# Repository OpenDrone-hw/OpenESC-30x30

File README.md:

# OpenESC-30x30

Open source 4-in-1 BLDC ESC with a 30.5 x 30.5 mm mounting pattern, part of the
incutec OpenDrone line. Four independent motor controllers, each with its own
MCU, gate driver and six MOSFETs, running AM32 and taking DShot over the
standard 8-pin connector.

Maintained by [@Just4Stan](https://github.com/Just4Stan).

## Specifications

| | |
|---|---|
| Continuous | 60 A / channel |
| Firmware | AM32 |
| ESC protocol | DShot, bidirectional |
| Telemetry | Extended DShot |
| Input | 2-8S LiPo (6.0-33.6 V) |
| BEC | None |
| MCU | One per motor |
| MOSFETs | 6 per motor |
| Current sense | On-board, 330 A |
| FC connector | JST-SH 8-pin |
| Mounting | 30.5 x 30.5 mm, 4.0 mm holes |
| Dimensions | 41.6 x 42.5 mm |
| PCB | 6-layer, 1.6 mm, 2 oz copper |

Technical write-up, part list and layout constraints: [AGENTS.md](AGENTS.md).

## In the line

What pairs with what, and what is available:
[opendrone.be](https://opendrone.be).

## Contributing

See [CONTRIBUTING.md](CONTRIBUTING.md).

## License

Hardware licensed under [CERN-OHL-S-2.0](https://ohwr.org/cern_ohl_s_v2.txt),
see [LICENSE](LICENSE).

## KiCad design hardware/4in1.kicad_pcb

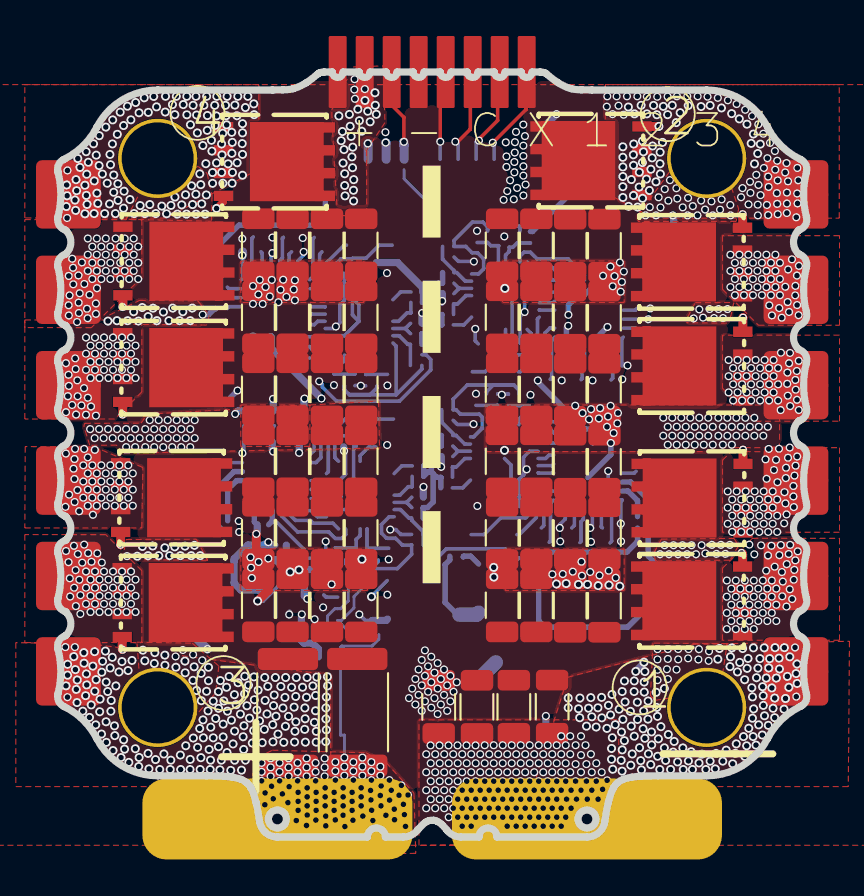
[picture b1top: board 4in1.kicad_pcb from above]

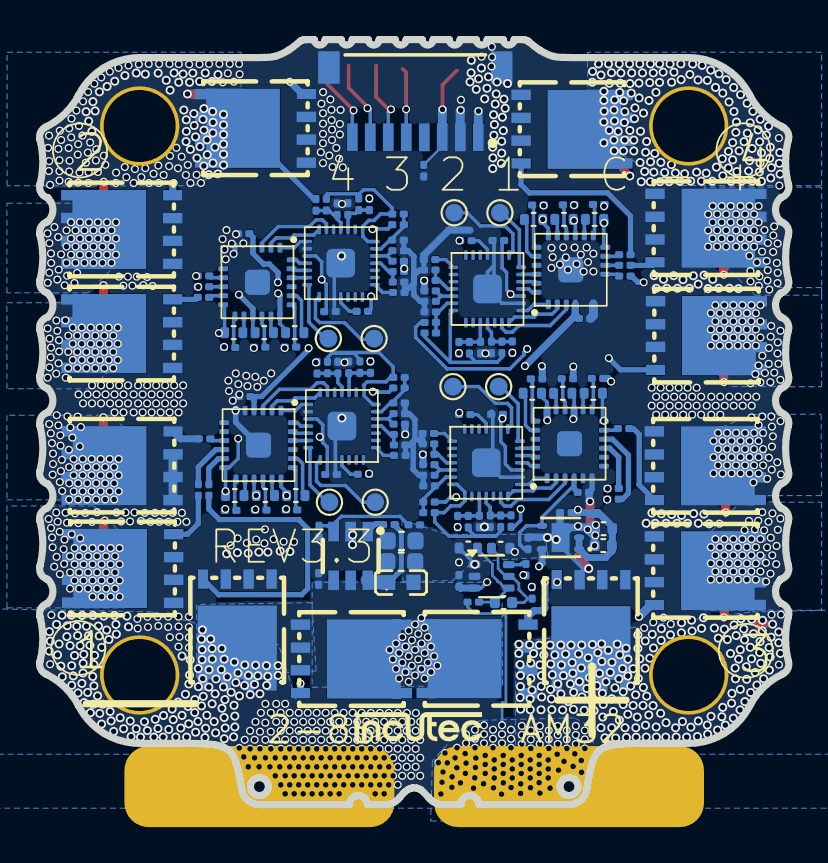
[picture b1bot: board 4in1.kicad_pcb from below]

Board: 6 copper layers, 41.6 x 42.5 mm, 222 parts (157 on the bottom side), 152 nets.

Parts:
C2, C2#2, C3, C3#2, C6, C8, C9, C13, C13#2, C13#3, C14, C14#2, C14#3, C17, C18, C26, C26#2, C26#3, C27, C27#2, C27#3, C30, C43, C43#2, C43#3, C44, C44#2, C44#3, C69, C70, C82, C82#2, C82#3, C83, C83#2, C83#3, C84, C84#2, C84#3, C85, C85#2, C85#3, C96, C97, C98, C99, C107, C107#2, C107#3, C108, C108#2, C108#3: 4.7uF; C_1206_3216Metric
C4, C51: 22uF; C_0402_1005Metric
C32, C33, C34, C35, C36, C37, C38, C39, C40, C41, C53, C56, C62, C67: 100nF; C_0402_WIDE
C42: 1uF; C_0402_1005Metric
C47, C86: 22uF; C_0603_1608Metric
C48, C49, C50, C52, C54, C55, C57, C58, C59, C60, C61, C63, C64, C65, C66, C68, C74, C75, C76, C81, C93, C94: 100nF; C_0201_0603Metric
J1: SM08B-SRSS-TB; JST_SM08B-SRSS-TB
Q1, Q2, Q3, Q4, Q5, Q6, Q7, Q8, Q9, Q10, Q11, Q12, Q13, Q14, Q15, Q16, Q17, Q18, Q19, Q20, Q21, Q22, Q23, Q24: SP40N01GHNK; PDFN-8L_L6.0-W5.0-P1.27
R10, R12, R13, R15, R25, R27, R28, R30, R31, R33, R34, R36, R46, R48, R49, R51, R52, R54, R64, R66, R67, R69, R70, R72: 10k; C_0201_0603Metric
R11, R14, R26, R29, R32, R35, R47, R50, R53, R65, R68, R71, R73, R89, R90: 1k; C_0201_0603Metric
R18, R19, R21, R22, R40, R41, R58, R59, R121: 10k; R_0201_0603Metric
R20, R39, R57, R87: 220R; R_0201_0603Metric
R23, R24, R37, R38, R42, R43, R44, R45, R55, R56, R60, R61, R62, R63, R74, R75, R76, R77, R78, R79, R80, R81, R82, R83: 15R; R_0201_0603Metric
R84, R85, R86, R88: 10R; R_0201_0603Metric
R120: 115k; R_0201_0603Metric
Rsense1, Rsense2: 0.2mR; R_2512_6332Metric
TP1, TP2, TP3, TP4, TP5, TP6, TP7, TP8: TestPoint; TestPoint_Pad_D1.0mm
U2, U5, U7, U9: AT32F421G8U7; QFN-28_L4.0-W4.0-P0.40-TL-EP2.4
U3: 4in1ESC30x30
U4, U6, U8, U10: NSG2065Q; QFN-24_L4.0-W4.0-P0.50-TL-EP2.8
U12: INA186A3IDCKR; SOT-363_SC-70-6
U13: LMR54406DBVR; SOT-23-6_L2.9-W1.6-P0.95-LS2.8-BR
U14: FTC160808S4R7MBCA; IND-SMD_L1.6-W0.8_FTC160865SR47MBCA
U15: TLV76733DRVR; WSON-6_L2.0-W2.0-P0.65-TL-EP

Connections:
+3V3: C4.2, C49.1, C51.2, C55.1, C61.1, C66.1, C81.1, C93.1, R18.2, R21.2, R40.2, R58.2, R84.2, R85.2, R86.2, R88.2, U2.17 (VDD), U5.17 (VDD), U7.17 (VDD), U9.17 (VDD), U12.3 (VS), U15.1 (OUT), U15.2 (FB/SNS)
+10V: C47.1, C57.1, C58.1, C63.1, C68.1, C76.1, C86.1, R120.1, U4.4 (VCC), U6.4 (VCC), U8.4 (VCC), U10.4 (VCC), U14.2, U15.4 (EN), U15.6 (IN)
+BATT: C2.1, C2#2.1, C3.1, C3#2.1, C6.1, C8.1, C9.1, C13.1, C13#2.1, C13#3.1, C14.1, C14#2.1, C14#3.1, C17.1, C18.1, C26.1, C26#2.1, C26#3.1, C27.1, C27#2.1, C27#3.1, C30.1, C43.1, C43#2.1, C43#3.1, C44.1, C44#2.1, C44#3.1, C69.1, C70.1, C74.1, C82.1, C82#2.1, C82#3.1, C83.1, C83#2.1, C83#3.1, C84.1, C84#2.1, C84#3.1, C85.1, C85#2.1, C85#3.1, C96.1, C97.1, C98.1, C99.1, C107.1, C107#2.1, C107#3.1, C108.1, C108#2.1, C108#3.1, J1.1, Q1.3 (D), Q6.3 (D), Q7.3 (D), Q8.3 (D), Q9.3 (D), Q10.3 (D), Q13.3 (D), Q16.3 (D), Q17.3 (D), Q18.3 (D), Q19.3 (D), Q20.3 (D), R89.2, Rsense1.2, Rsense2.2, U3.3 (VBAT+), U13.4 (EN), U13.5 (VIN)
/CSA+: R90.2, Rsense1.1, Rsense2.1, U3.1 (VBAT)
/CURR: C94.1, J1.3, R73.1, U3.5 (CUR)
/ESC1/AH: U2.20 (PA10), U4.22 (HIN1)
/ESC1/AL: U2.15 (PB1), U4.1 (LIN1)
/ESC1/BH: U2.19 (PA9), U4.23 (HIN2)
/ESC1/BL: U2.14 (PB0), U4.2 (LIN2)
/ESC1/CH: U2.18 (PA8), U4.24 (HIN3)
/ESC1/CL: U2.13 (PA7), U4.3 (LIN3)
/ESC1/FBA: R25.1, R26.2, R27.2, U2.6 (PA0)
/ESC1/FBB: R28.2, R29.2, R30.2, U2.10 (PA4)
/ESC1/FBC: R31.2, R32.2, R33.2, U2.11 (PA5)
/ESC1/FBCOMMON: R25.2, R28.1, R31.1, U2.7 (PA1)
/ESC1/GHA: R76.1, U4.19 (HO1)
/ESC1/GHB: R55.1, U4.16 (HO2)
/ESC1/GHC: R23.1, U4.13 (HO3)
/ESC1/GLA: R80.1, U4.11 (LO1)
/ESC1/GLB: R62.1, U4.10 (LO2)
/ESC1/GLC: R42.1, U4.9 (LO3)
/ESC1/MotorA: C53.1, Q1.1 (S), Q2.3 (D), R27.1, U3.23 (1A), U4.18 (VS1)
/ESC1/MotorB: C32.1, Q6.1 (S), Q11.3 (D), R30.1, U3.22 (1B), U4.15 (VS2)
/ESC1/MotorC: C36.1, Q16.1 (S), Q21.3 (D), R33.1, U3.21 (1C), U4.12 (VS3)
/ESC1/vdda: C48.1, R84.1, U2.5 (VDDA)
/ESC2/AH: U5.20 (PA10), U6.22 (HIN1)
/ESC2/AL: U5.15 (PB1), U6.1 (LIN1)
/ESC2/BH: U5.19 (PA9), U6.23 (HIN2)
/ESC2/BL: U5.14 (PB0), U6.2 (LIN2)
/ESC2/CH: U5.18 (PA8), U6.24 (HIN3)
/ESC2/CL: U5.13 (PA7), U6.3 (LIN3)
/ESC2/FBA: R10.1, R11.2, R12.2, U5.6 (PA0)
/ESC2/FBB: R13.2, R14.2, R15.2, U5.10 (PA4)
/ESC2/FBC: R34.2, R35.2, R36.2, U5.11 (PA5)
/ESC2/FBCOMMON: R10.2, R13.1, R34.1, U5.7 (PA1)
/ESC2/GHA: R77.1, U6.19 (HO1)
/ESC2/GHB: R56.1, U6.16 (HO2)
/ESC2/GHC: R24.1, U6.13 (HO3)
/ESC2/GLA: R81.1, U6.11 (LO1)
/ESC2/GLB: R63.1, U6.10 (LO2)
/ESC2/GLC: R43.1, U6.9 (LO3)
/ESC2/MotorA: C56.1, Q3.3 (D), Q7.1 (S), R12.1, U3.20 (2B), U6.18 (VS1)
/ESC2/MotorB: C33.1, Q8.1 (S), Q12.3 (D), R15.1, U3.19 (2C), U6.15 (VS2)
/ESC2/MotorC: C37.1, Q17.1 (S), Q22.3 (D), R36.1, U3.18 (2A), U6.12 (VS3)
/ESC2/vdda: C54.1, R85.1, U5.5 (VDDA)
/ESC3/AH: U7.20 (PA10), U8.22 (HIN1)
/ESC3/AL: U7.15 (PB1), U8.1 (LIN1)
/ESC3/BH: U7.19 (PA9), U8.23 (HIN2)
/ESC3/BL: U7.14 (PB0), U8.2 (LIN2)
/ESC3/CH: U7.18 (PA8), U8.24 (HIN3)
/ESC3/CL: U7.13 (PA7), U8.3 (LIN3)
/ESC3/FBA: R46.1, R47.2, R48.2, U7.6 (PA0)
/ESC3/FBB: R49.2, R50.2, R51.2, U7.10 (PA4)
/ESC3/FBC: R52.2, R53.2, R54.2, U7.11 (PA5)
/ESC3/FBCOMMON: R46.2, R49.1, R52.1, U7.7 (PA1)
/ESC3/GHA: R78.1, U8.19 (HO1)
/ESC3/GHB: R60.1, U8.16 (HO2)
/ESC3/GHC: R37.1, U8.13 (HO3)
/ESC3/GLA: R82.1, U8.11 (LO1)
/ESC3/GLB: R74.1, U8.10 (LO2)
/ESC3/GLC: R44.1, U8.9 (LO3)
/ESC3/MotorA: C62.1, Q4.3 (D), Q13.1 (S), R48.1, U3.15 (3B), U8.18 (VS1)
/ESC3/MotorB: C34.1, Q9.1 (S), Q14.3 (D), R51.1, U3.16 (3C), U8.15 (VS2)
/ESC3/MotorC: C38.1, Q18.1 (S), Q23.3 (D), R54.1, U3.17 (3A), U8.12 (VS3)
/ESC3/vdda: C60.1, R86.1, U7.5 (VDDA)
/ESC4/AH: U9.20 (PA10), U10.22 (HIN1)
/ESC4/AL: U9.15 (PB1), U10.1 (LIN1)
/ESC4/BH: U9.19 (PA9), U10.23 (HIN2)
/ESC4/BL: U9.14 (PB0), U10.2 (LIN2)
/ESC4/CH: U9.18 (PA8), U10.24 (HIN3)
/ESC4/CL: U9.13 (PA7), U10.3 (LIN3)
/ESC4/FBA: R64.1, R65.2, R66.2, U9.6 (PA0)
/ESC4/FBB: R67.2, R68.2, R69.2, U9.10 (PA4)
/ESC4/FBC: R70.2, R71.2, R72.2, U9.11 (PA5)
/ESC4/FBCOMMON: R64.2, R67.1, R70.1, U9.7 (PA1)
/ESC4/GHA: R79.1, U10.19 (HO1)
/ESC4/GHB: R61.1, U10.16 (HO2)
/ESC4/GHC: R38.1, U10.13 (HO3)
/ESC4/GLA: R83.1, U10.11 (LO1)
/ESC4/GLB: R75.1, U10.10 (LO2)
/ESC4/GLC: R45.1, U10.9 (LO3)
/ESC4/MotorA: C67.1, Q5.3 (D), Q19.1 (S), R66.1, U3.12 (4A), U10.18 (VS1)
/ESC4/MotorB: C35.1, Q10.1 (S), Q15.3 (D), R69.1, U3.13 (4B), U10.15 (VS2)
/ESC4/MotorC: C39.1, Q20.1 (S), Q24.3 (D), R72.1, U3.14 (4C), U10.12 (VS3)
/ESC4/vdda: C65.1, R88.1, U9.5 (VDDA)
/M1: J1.5, R20.1, U3.7 (M1)
/M2: J1.6, R39.1, U3.8 (M2)
/M3: J1.7, R57.1, U3.9 (M3)
/M4: J1.8, R87.1, U3.10 (M4)
GND: C2.2, C2#2.2, C3.2, C3#2.2, C4.1, C6.2, C8.2, C9.2, C13.2, C13#2.2, C13#3.2, C14.2, C14#2.2, C14#3.2, C17.2, C18.2, C26.2, C26#2.2, C26#3.2, C27.2, C27#2.2, C27#3.2, C30.2, C40.2, C41.2, C43.2, C43#2.2, C43#3.2, C44.2, C44#2.2, C44#3.2, C47.2, C48.2, C49.2, C50.2, C51.1, C52.2, C54.2, C55.2, C57.2, C58.2, C59.2, C60.2, C61.2, C63.2, C64.2, C65.2, C66.2, C68.2, C69.2, C70.2, C74.2, C76.2, C81.2, C82.2, C82#2.2, C82#3.2, C83.2, C83#2.2, C83#3.2, C84.2, C84#2.2, C84#3.2, C85.2, C85#2.2, C85#3.2, C86.2, C93.2, C94.2, C96.2, C97.2, C98.2, C99.2, C107.2, C107#2.2, C107#3.2, C108.2, C108#2.2, C108#3.2, J1.2, J1.P1 (MP1), J1.P2 (MP2), Q2.1 (S), Q3.1 (S), Q4.1 (S), Q5.1 (S), Q11.1 (S), Q12.1 (S), Q14.1 (S), Q15.1 (S), Q21.1 (S), Q22.1 (S), Q23.1 (S), Q24.1 (S), R11.1, R14.1, R19.2, R22.2, R26.1, R29.1, R32.1, R35.1, R41.2, R47.1, R50.1, R53.1, R59.2, R65.1, R68.1, R71.1, R121.2, U2.16 (VSS), U2.29 (VSS), U3.2 (BATGND), U3.4 (GND), U3.11 (Hole), U4.6 (COM), U4.25 (COM), U5.16 (VSS), U5.29 (VSS), U6.6 (COM), U6.25 (COM), U7.16 (VSS), U7.29 (VSS), U8.6 (COM), U8.25 (COM), U9.16 (VSS), U9.29 (VSS), U10.6 (COM), U10.25 (COM), U12.1 (REF), U12.2 (GND), U13.2 (GND), U15.3 (GND), U15.5 (GND), U15.7 (EP)
unnamed: Q1.2 (G), R76.2
unnamed: Q2.2 (G), R80.2
unnamed: Q3.2 (G), R81.2
unnamed: Q4.2 (G), R82.2
unnamed: Q5.2 (G), R83.2
unnamed: Q6.2 (G), R55.2
unnamed: Q7.2 (G), R77.2
unnamed: Q8.2 (G), R56.2
unnamed: Q9.2 (G), R60.2
unnamed: Q10.2 (G), R61.2
unnamed: Q11.2 (G), R62.2
unnamed: Q12.2 (G), R63.2
unnamed: Q13.2 (G), R78.2
unnamed: Q14.2 (G), R74.2
unnamed: Q15.2 (G), R75.2
unnamed: Q16.2 (G), R23.2
unnamed: Q17.2 (G), R24.2
unnamed: Q18.2 (G), R37.2
unnamed: Q19.2 (G), R79.2
unnamed: Q20.2 (G), R38.2
unnamed: Q21.2 (G), R42.2
unnamed: Q22.2 (G), R43.2
unnamed: Q23.2 (G), R44.2
unnamed: Q24.2 (G), R45.2
unnamed: R19.1, U2.1 (BOOT0)
unnamed: C50.1, R18.1, U2.4 (NRST)
unnamed: TP1.1 (1_1), U2.21 (PA13)
unnamed: TP4.1 (1_1), U2.22 (PA14)
unnamed: R20.2, U2.25 (PB4)
unnamed: C53.2, U4.20 (VB1)
unnamed: C32.2, U4.17 (VB2)
unnamed: C36.2, U4.14 (VB3)
unnamed: R22.1, U5.1 (BOOT0)
unnamed: C52.1, R21.1, U5.4 (NRST)
unnamed: TP2.1 (1_1), U5.21 (PA13)
unnamed: TP5.1 (1_1), U5.22 (PA14)
unnamed: R39.2, U5.25 (PB4)
unnamed: C56.2, U6.20 (VB1)
unnamed: C33.2, U6.17 (VB2)
unnamed: C37.2, U6.14 (VB3)
unnamed: R41.1, U7.1 (BOOT0)
unnamed: C59.1, R40.1, U7.4 (NRST)
unnamed: TP3.1 (1_1), U7.21 (PA13)
unnamed: TP6.1 (1_1), U7.22 (PA14)
unnamed: R57.2, U7.25 (PB4)
unnamed: C62.2, U8.20 (VB1)
unnamed: C34.2, U8.17 (VB2)
unnamed: C38.2, U8.14 (VB3)
unnamed: R59.1, U9.1 (BOOT0)
unnamed: C64.1, R58.1, U9.4 (NRST)
unnamed: TP7.1 (1_1), U9.21 (PA13)
unnamed: TP8.1 (1_1), U9.22 (PA14)
unnamed: R87.2, U9.25 (PB4)
unnamed: C67.2, U10.20 (VB1)
unnamed: C35.2, U10.17 (VB2)
unnamed: C39.2, U10.14 (VB3)
unnamed: C41.1, C42.2, R90.1, U12.4 (+IN)
unnamed: C40.1, C42.1, R89.1, U12.5 (-IN)
unnamed: R73.2, U12.6 (OUT)
unnamed: C75.2, U13.1 (CB)
unnamed: R120.2, R121.1, U13.3 (FB)
unnamed: C75.1, U13.6 (SW), U14.1

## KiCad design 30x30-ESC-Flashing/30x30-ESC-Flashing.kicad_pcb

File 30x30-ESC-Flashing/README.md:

# 30x30-ESC-Flashing: AM32 SWD flashing station

SWD flashing jig for the **OpenESC-30x30** (`../hardware/4in1`). Retargeted copy
of `OpenESC-20x20/20x20-ESC-Flashing`: same 100 x 100 mm 4-layer layout, same
pogo pins, headers, banana jacks and M3 pattern. Only the ten pogo pins moved,
to the coordinates the 30x30 actually uses.

## Contacts

Ten 1.2 mm SMD pogo pins land on the ESC's B.Cu face, which is where the SWD
test points are:

| Net | Lands on |
|---|---|
| `/SWD1_CLK` … `/SWD4_CLK` | PA14 test point of each channel |
| `/SWD1_DIO` … `/SWD4_DIO` | PA13 test point of each channel |
| `/VBAT`, `GND` | the two battery pads, so the target is powered while flashing |

Channel numbering comes from the ESC schematic sheets (`/ESC1/` … `/ESC4/`), not
from position, so SWD1 really is channel 1.

Four 4-pin headers break out CLK, DIO and GND per channel for the ST-LINK probes.

## Retargeted, not redrawn

```bash
KPY=/Applications/KiCad/KiCad.app/Contents/Frameworks/Python.framework/Versions/Current/bin/python3
$KPY ~/OpenDrone/software/OpenDrone-Scripts/esc/esc_jig_retarget.py \
    ../../OpenESC-20x20/20x20-ESC-Flashing/20x20-ESC-Flashing.kicad_pcb \
    ../hardware/4in1.kicad_pcb --dut 4in1ESC30x30 \
    --strip-tracks --swap-outline 30 --retext "20x20=30x30" \
    --out 30x30-ESC-Flashing.kicad_pcb
```

`--strip-tracks` clears the 20x20 routing, `--swap-outline` replaces the
silkscreen ESC outline with the 30x30 one. **The board is unrouted**: the
copper pours from the template are still in place and no longer match the new
pin positions, so redo them.

## Flashing

Two-stage, as on the 20x20: SWD once per MCU to clear readout protection and
write the AM32 bootloader, then firmware and settings over the DShot signal pin.
Host side is `../../OpenESC-20x20/hardware/flash_openesc20.sh` (OpenOCD,
AT32F421 FAP unlock, verify, `--loop` for batches).

License: hardware CERN-OHL-S-2.0, same as the parent repo.

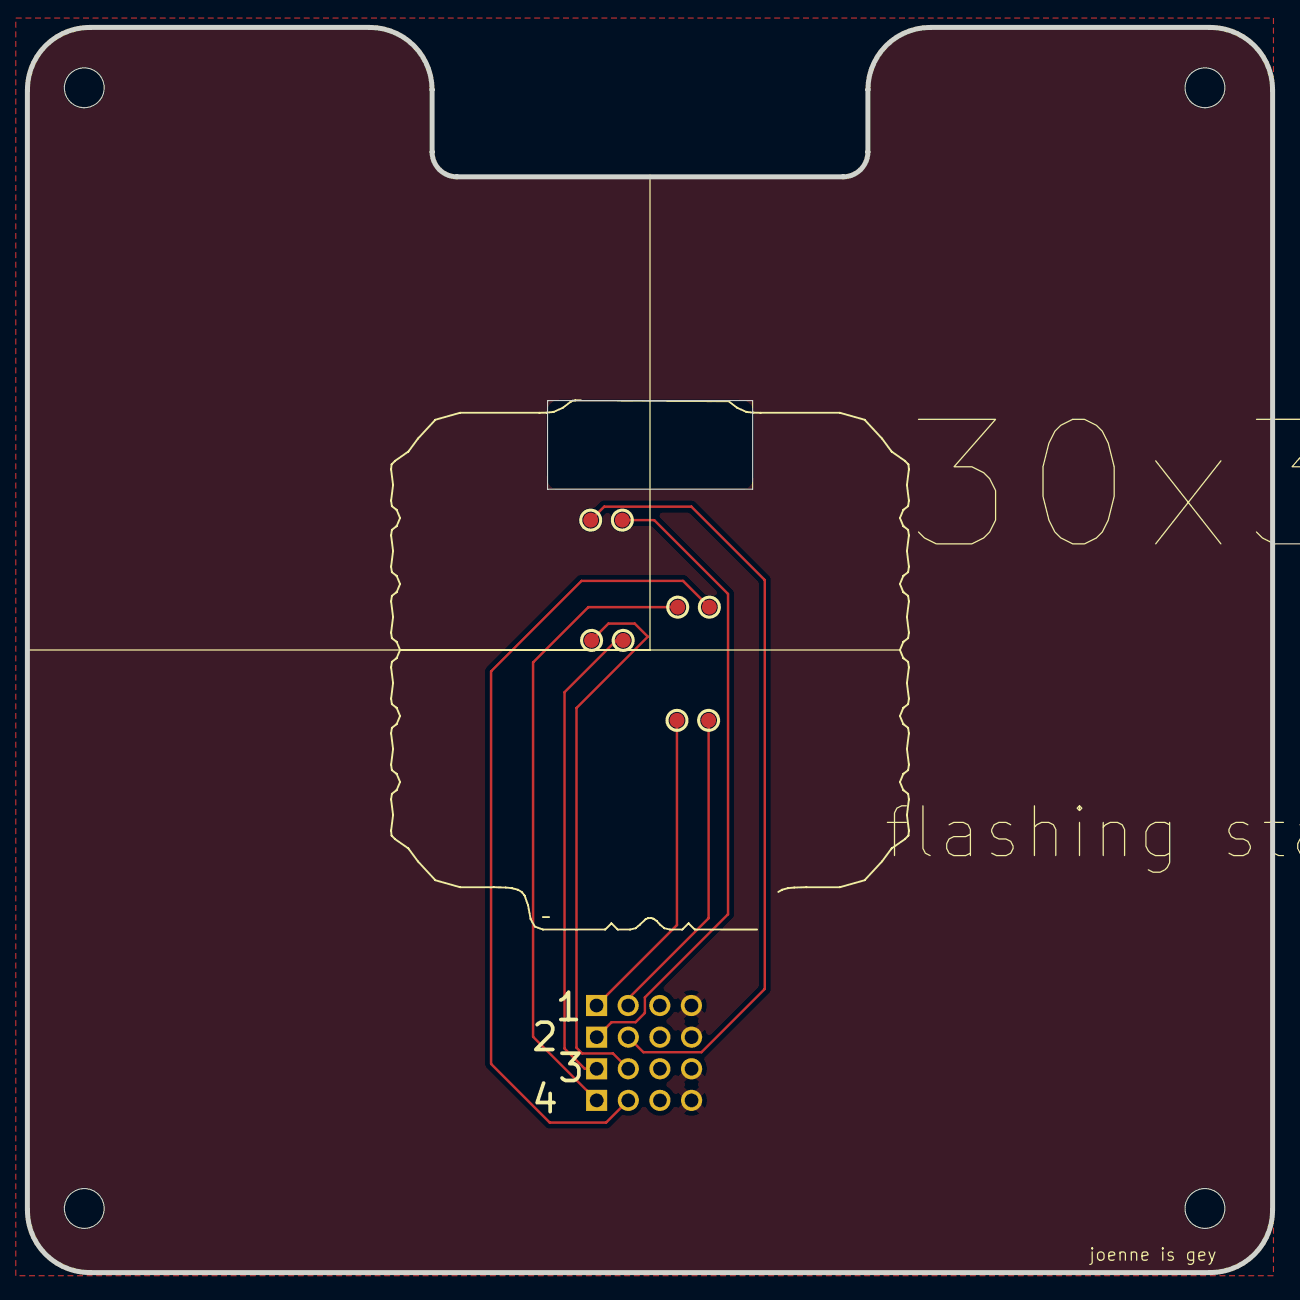
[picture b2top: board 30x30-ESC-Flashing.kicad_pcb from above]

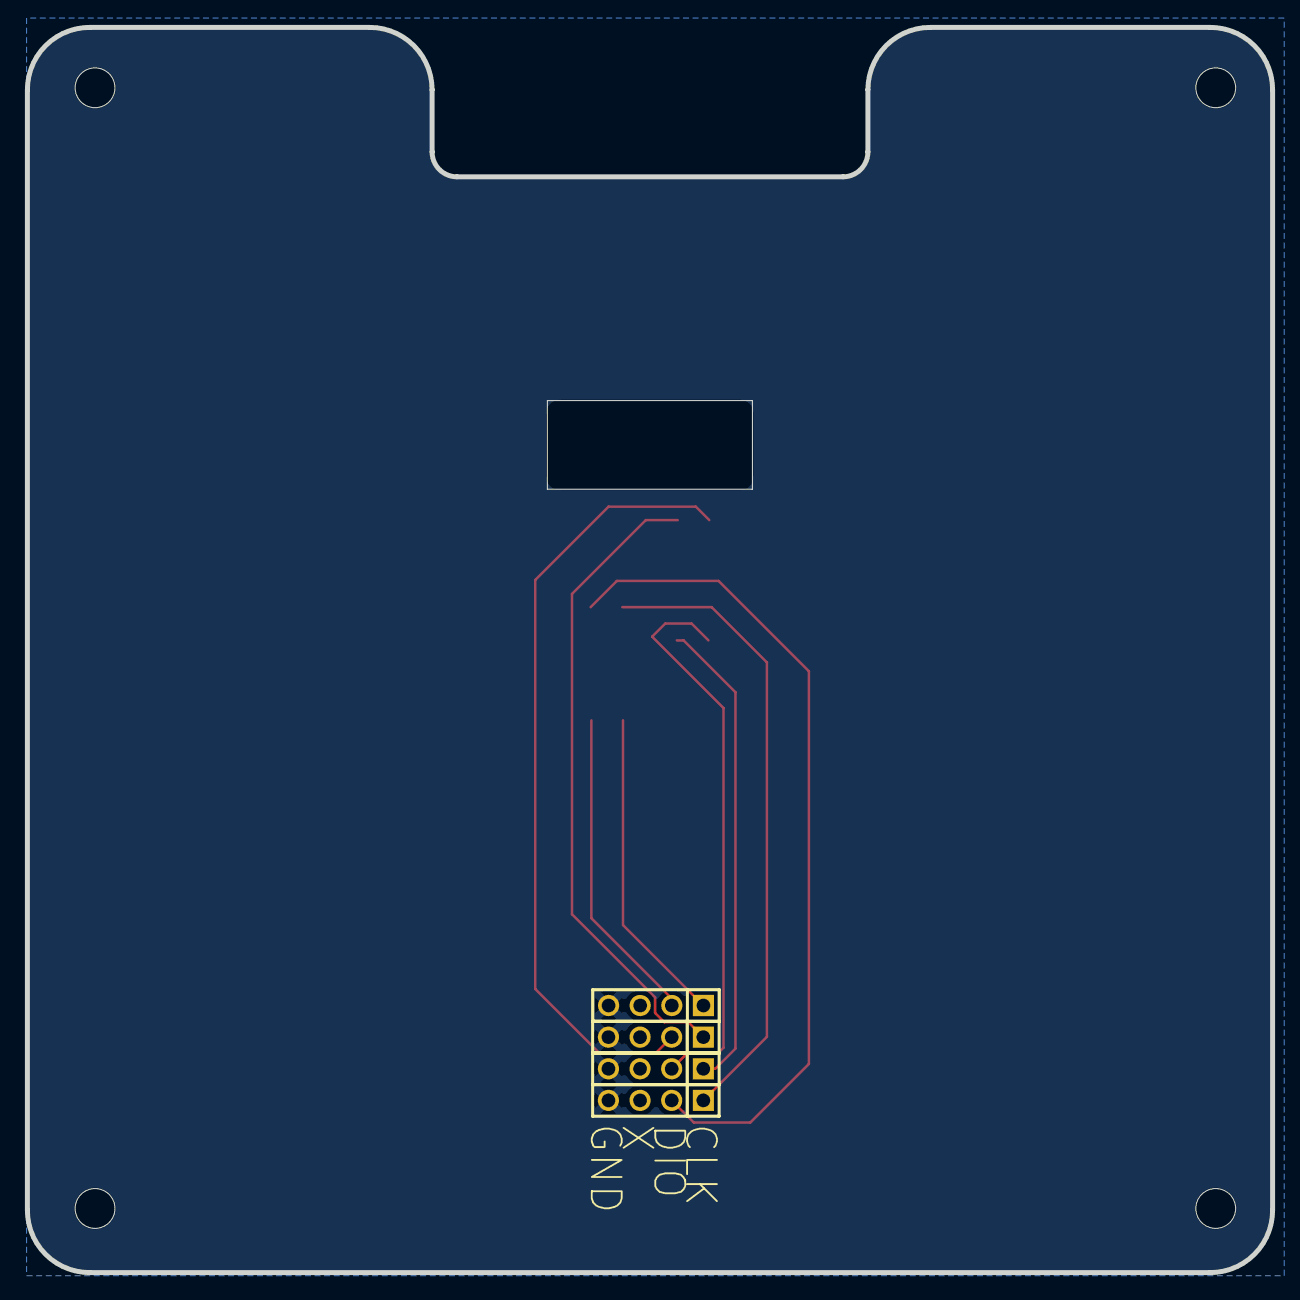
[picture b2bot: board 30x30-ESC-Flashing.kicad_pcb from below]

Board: 4 copper layers, 100.0 x 100.0 mm, 16 parts (4 on the bottom side), 9 nets.

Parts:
H1, H2, H3, H4: MountingHole; MountingHole_3.2mm_M3
J1, J3, J5, J6: SWD1; HDR-TH_4P-P2.54-V-M
TP1, TP2, TP3, TP4, TP5, TP6, TP7, TP8: YZ118311024R-02; CONN-SMD_BD1.2_YZ118311024R-02

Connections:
/SWD1_CLK: J1.1, TP7.1
/SWD1_DIO: J1.2, TP8.1
/SWD2_CLK: J3.1, TP5.1
/SWD2_DIO: J3.2, TP6.1
/SWD3_CLK: J5.1, TP3.1
/SWD3_DIO: J5.2, TP4.1
/SWD4_CLK: J6.1, TP1.1
/SWD4_DIO: J6.2, TP2.1
GND: J1.4, J3.4, J5.4, J6.4
